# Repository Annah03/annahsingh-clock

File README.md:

# annahsingh-clock
 My first HPS clock.

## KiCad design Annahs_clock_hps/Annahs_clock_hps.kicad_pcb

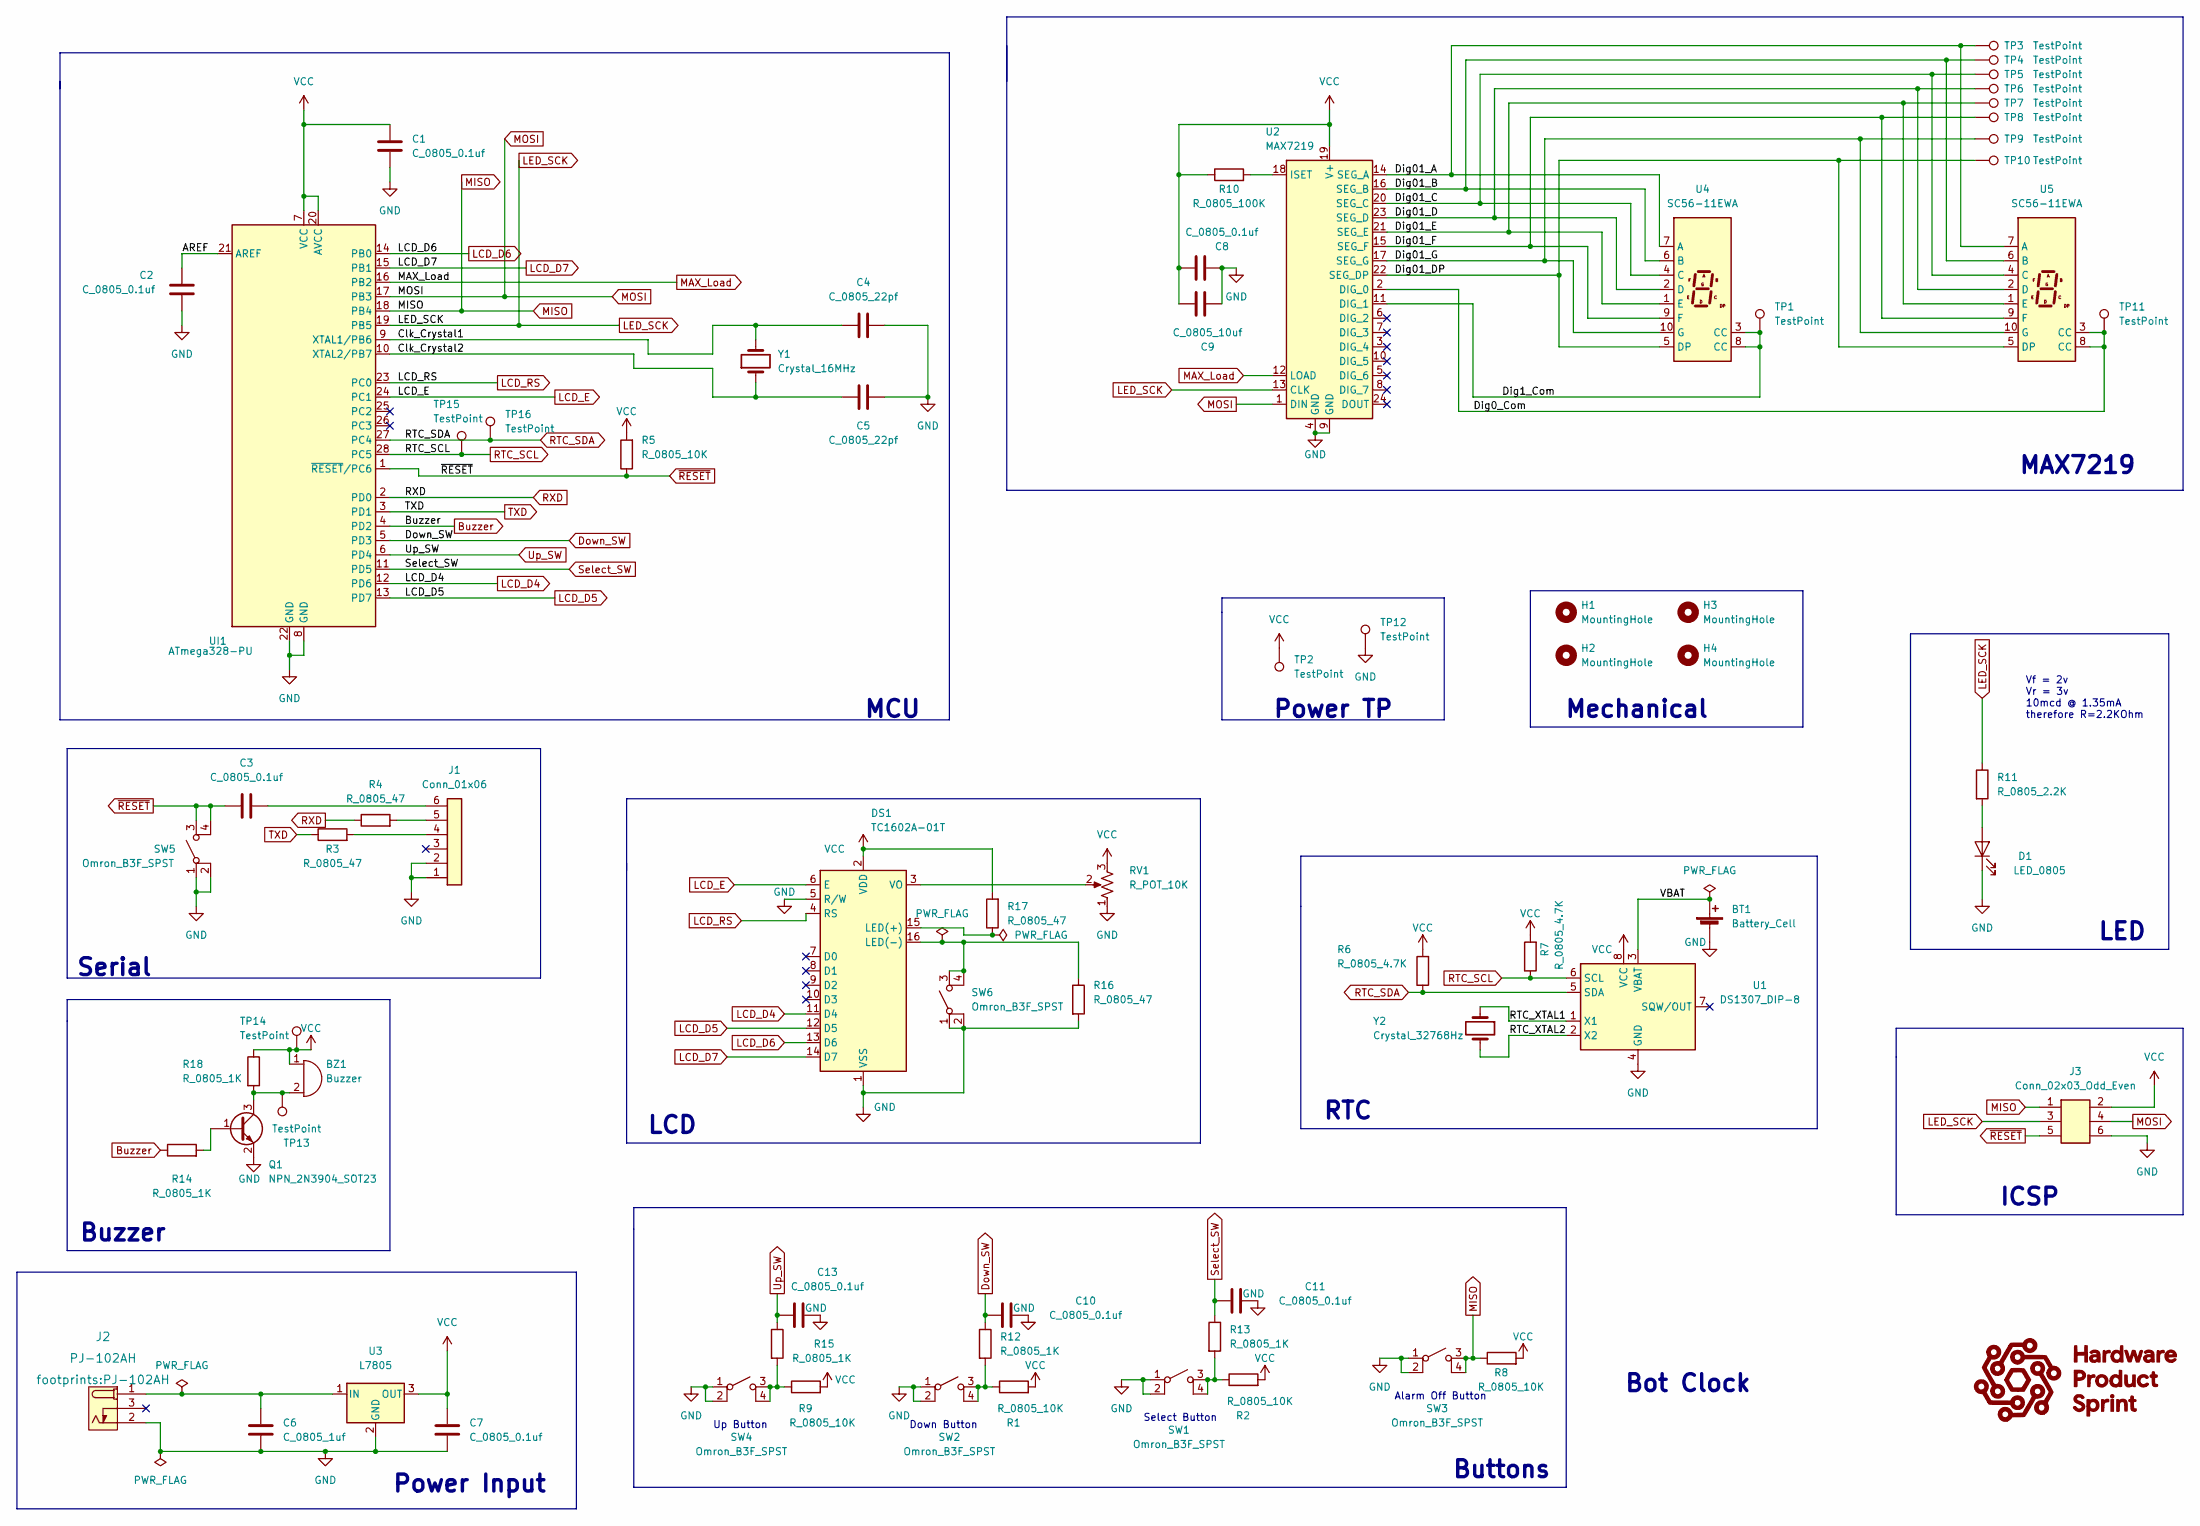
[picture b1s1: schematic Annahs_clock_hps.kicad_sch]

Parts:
BT1: Battery_Cell; BatteryHolder_Keystone_106_1x20mm; MPN BS-7; Digikey PN BS-7-ND
BZ1: Buzzer; Buzzer_TDK_PS1240P02BT_D12.2mm_H6.5mm; MPN PS1420P02CT; Digikey PN 445-2526-1-ND
C1, C2, C3, C7, C8, C10, C11, C13: C_0805_0.1uf; C_0805_2012Metric; Voltage N/A; Tolerance N/A; MPN 08055C104KAT2A; Digikey PN 478-1395-1-ND
C4, C5: C_0805_22pf; C_0805_2012Metric; Voltage N/A; Tolerance N/A; MPN CC0805JRNPO9BN220; Digikey PN 311-1103-1-ND
C6: C_0805_1uf; C_0805_2012Metric; Voltage N/A; Tolerance N/A; MPN CC0805KKX7R8BB105; Digikey PN 311-1456-1-ND
C9: C_0805_10uf; C_0805_2012Metric; Voltage N/A; Tolerance N/A; MPN GRM21BR61E106KA73L; Digikey PN 490-5523-1-ND
D1: LED_0805; LED_0805_2012Metric; MPN 150080RS75000; Digikey PN 732-4984-1-ND
DS1: TC1602A-01T; MPN 1447; Digikey PN 1528-2212-ND
H1, H2, H3, H4: MountingHole; MountingHole_3.2mm_M3
J1: Conn_01x06; PinHeader_1x06_P2.54mm_Vertical; MPN 61300611121; Digikey PN 732-5319-ND
J2: PJ-102AH; MPN PJ-102AH; Digikey PN CP-102AH-ND
J3: Conn_02x03_Odd_Even; PinHeader_2x03_P2.54mm_Vertical; MPN PRPC003DAAN-RC; Digikey PN S2011EC-03-ND
Q1: NPN_2N3904_SOT23; SOT-23; MPN CMPT3904E TR PBFREE; Digikey PN 1514-CMPT3904ETRPBFREECT-ND
R1, R2, R5, R8, R9: R_0805_10K; R_0805_2012Metric; Tolerance N/A; MPN RC0805FR-0710KL; Digikey PN 311-10.0KCRCT-ND
R3, R4, R16, R17: R_0805_47; R_0805_2012Metric; Tolerance N/A; Mouser PN N/A; Digikey PN RC0805FR-0747RL
R6, R7: R_0805_4.7K; R_0805_2012Metric; Tolerance N/A; MPN RC0805FR-074K7L; Digikey PN 311-4.70KCRCT-ND
R10: R_0805_100K; R_0805_2012Metric; Tolerance N/A; MPN RC0805FR-07100KL; Digikey PN 311-100KCRCT-ND
R11: R_0805_2.2K; R_0805_2012Metric; Tolerance N/A; MPN N/A; Digikey PN 311-2.20KCRCT-ND
R12, R13, R14, R15, R18: R_0805_1K; R_0805_2012Metric; Tolerance N/A; Mouser PN N/A; Digikey PN RC0805FR-0710KL
RV1: R_POT_10K; Potentiometer_Bourns_3386P_Vertical; MPN 3386P-1-103TLF; Digikey PN 3386P-103TLF-ND
SW1, SW2, SW3, SW4, SW5, SW6: Omron_B3F_SPST; SW_SPST_Omron_B3FS-100xP; MPN B3FS-1000P; Digikey PN SW423CT-ND
TP1, TP2, TP3, TP4, TP5, TP6, TP7, TP8, TP9, TP10, TP11, TP12, TP13, TP14, TP15, TP16: TestPoint; TestPoint_THTPad_D2.0mm_Drill1.0mm
U1: DS1307_DIP-8; DIP-8_W7.62mm; MPN A 08-LC-TT; Digikey PN AE9986-ND
U2: MAX7219; DIP-24_W7.62mm; MPN ED241DT; Digikey PN ED3049-5-ND
U3: L7805; TO-252-2; MPN L7805CDT-TR; Digikey PN 497-7255-1-ND
U4, U5: SC56-11EWA; Sx56-1xxxxx; Digikey PN 754-1465-5-ND
UI1: ATmega328-PU; DIP-28_W7.62mm; MPN ED281DT; Digikey PN ED3050-5-ND
Y1: Crystal_16MHz; Crystal_SMD_HC49-SD; MPN ECS-160-20-5PXDN-TR; Digikey PN XC1299CT-ND
Y2: Crystal_32768Hz; Crystal_SMD_2Pin_3.2x1.5mm; MPN Q 0,032768-JTX310-12,5-20-T1-HMR-50K-LF; Digikey PN 1908-1314-1-ND

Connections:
/AREF: C2.1, UI1.21 (AREF)
/Clk_Crystal1: C4.2, UI1.9 (XTAL1/PB6), Y1.2
/Clk_Crystal2: C5.1, UI1.10 (XTAL2/PB7), Y1.1
/Dig0_Com: TP11.1, U2.2 (DIG_0), U5.3 (CC), U5.8 (CC)
/Dig01_A: TP3.1, U2.14 (SEG_A), U4.7 (A), U5.7 (A)
/Dig01_B: TP4.1, U2.16 (SEG_B), U4.6 (B), U5.6 (B)
/Dig01_C: TP5.1, U2.20 (SEG_C), U4.4 (C), U5.4 (C)
/Dig1_Com: TP1.1, U2.11 (DIG_1), U4.3 (CC), U4.8 (CC)
/Dig01_D: TP6.1, U2.23 (SEG_D), U4.2 (D), U5.2 (D)
/Dig01_DP: TP10.1, U2.22 (SEG_DP), U4.5 (DP), U5.5 (DP)
/Dig01_E: TP7.1, U2.21 (SEG_E), U4.1 (E), U5.1 (E)
/Dig01_F: TP8.1, U2.15 (SEG_F), U4.9 (F), U5.9 (F)
/Dig01_G: TP9.1, U2.17 (SEG_G), U4.10 (G), U5.10 (G)
/RTC_XTAL1: U1.1 (X1), Y2.1
/RTC_XTAL2: U1.2 (X2), Y2.2
/VBAT: BT1.1 (+), U1.3 (VBAT)
Buzzer: R14.1, UI1.4 (PD2)
Down_SW: C10.2, R12.1, UI1.5 (PD3)
GND: BT1.2 (-), C1.2, C2.2, C4.1, C5.2, C6.2, C7.2, C8.2, C9.2, C10.1, C11.1, C13.1, D1.1 (K), DS1.1 (VSS), DS1.5 (R/W), J1.1, J1.2, J2.2 (OUT), J3.6, Q1.2 (E), R16.2, RV1.1, SW1.1 (A), SW1.2 (A), SW2.1 (A), SW2.2 (A), SW3.1 (A), SW3.2 (A), SW4.1 (A), SW4.2 (A), SW5.1 (A), SW5.2 (A), SW6.1 (A), SW6.2 (A), TP12.1, U1.4 (GND), U2.4 (GND), U2.9 (GND), U3.2 (GND), UI1.8 (GND), UI1.22 (GND)
LCD_D4: DS1.11 (D4), UI1.12 (PD6)
LCD_D5: DS1.12 (D5), UI1.13 (PD7)
LCD_D6: DS1.13 (D6), UI1.14 (PB0)
LCD_D7: DS1.14 (D7), UI1.15 (PB1)
LCD_E: DS1.6 (E), UI1.24 (PC1)
LCD_RS: DS1.4 (RS), UI1.23 (PC0)
LED_SCK: J3.3, R11.1, U2.13 (CLK), UI1.19 (PB5)
MAX_Load: U2.12 (LOAD), UI1.16 (PB2)
MISO: J3.1, R8.1, SW3.3 (B), SW3.4 (B), UI1.18 (PB4)
MOSI: J3.4, U2.1 (DIN), UI1.17 (PB3)
unnamed: BZ1.2 (+), Q1.3 (C), R18.2, TP13.1
unnamed: C3.2, J1.6
unnamed: C6.1, J2.1 (POLE), U3.1 (IN)
unnamed: D1.2 (A), R11.2
unnamed: DS1.3 (VO), RV1.2
unnamed: DS1.15 (LED(+)), R17.1
unnamed: DS1.16 (LED(-)), R16.1, SW6.3 (B), SW6.4 (B)
unnamed: J1.4, R3.2
unnamed: J1.5, R4.2
unnamed: Q1.1 (B), R14.2
unnamed: R1.1, R12.2, SW2.3 (B), SW2.4 (B)
unnamed: R10.2, U2.18 (ISET)
unnamed: R2.1, R13.2, SW1.3 (B), SW1.4 (B)
unnamed: R9.1, R15.2, SW4.3 (B), SW4.4 (B)
RTC_SCL: R7.1, TP15.1, U1.6 (SCL), UI1.28 (PC5)
RTC_SDA: R6.1, TP16.1, U1.5 (SDA), UI1.27 (PC4)
RXD: R4.1, UI1.2 (PD0)
Select_SW: C11.2, R13.1, UI1.11 (PD5)
TXD: R3.1, UI1.3 (PD1)
Up_SW: C13.2, R15.1, UI1.6 (PD4)
VCC: BZ1.1 (-), C1.1, C7.1, C8.1, C9.1, DS1.2 (VDD), J3.2, R1.2, R2.2, R5.2, R6.2, R7.2, R8.2, R9.2, R10.1, R17.2, R18.1, RV1.3, TP2.1, TP14.1, U1.8 (VCC), U2.19 (V+), U3.3 (OUT), UI1.7 (VCC), UI1.20 (AVCC)
~RESET: C3.1, J3.5, R5.1, SW5.3 (B), SW5.4 (B), UI1.1 (~RESET/PC6)

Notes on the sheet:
MCU
Down Button
Select Button
Mechanical
MAX7219
Power TP
LCD
Power Input
Buttons
Serial
Alarm Off Button
LED
RTC
Up Button
Vf = 2v Vr = 3v 10mcd @ 1.35mA therefore R=2.2KOhm
Bot Clock
ICSP
Buzzer

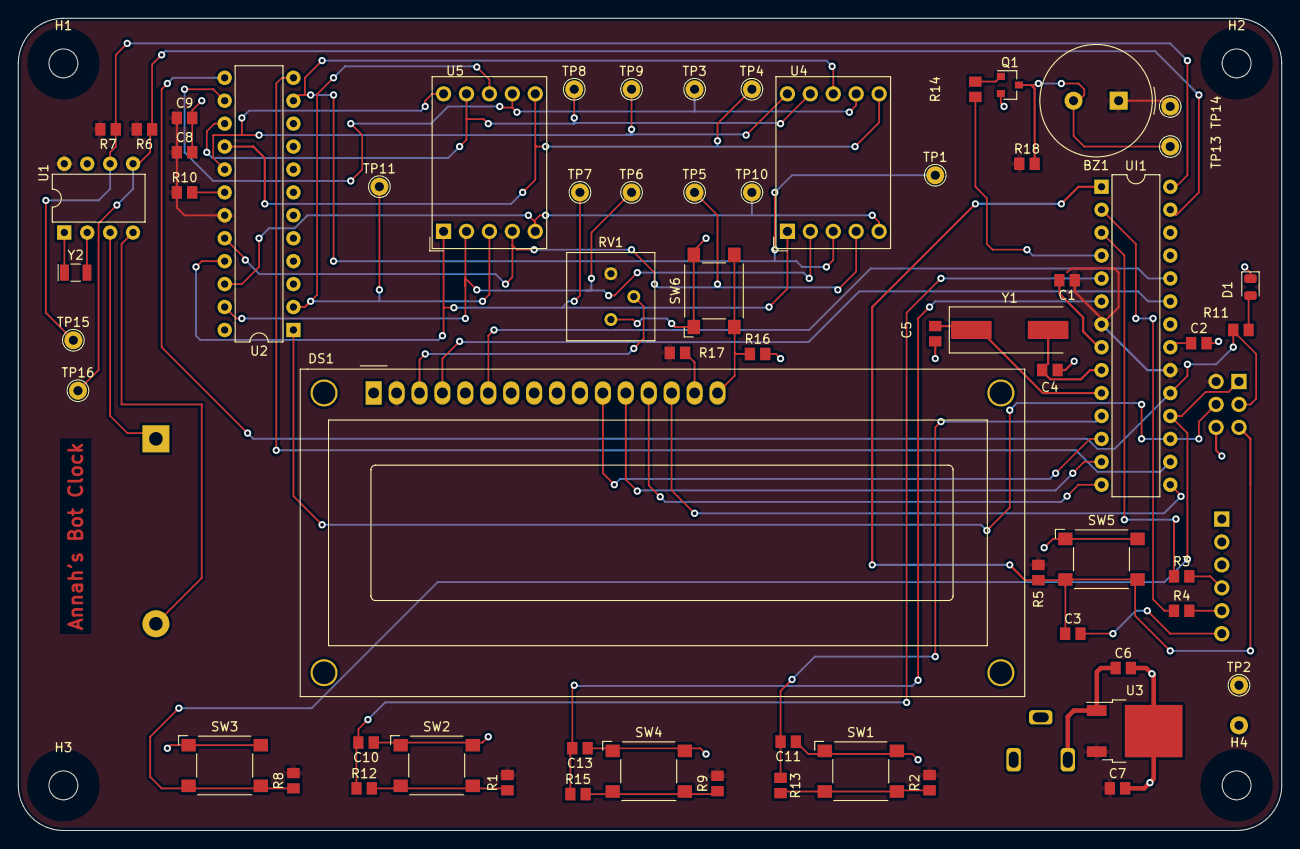
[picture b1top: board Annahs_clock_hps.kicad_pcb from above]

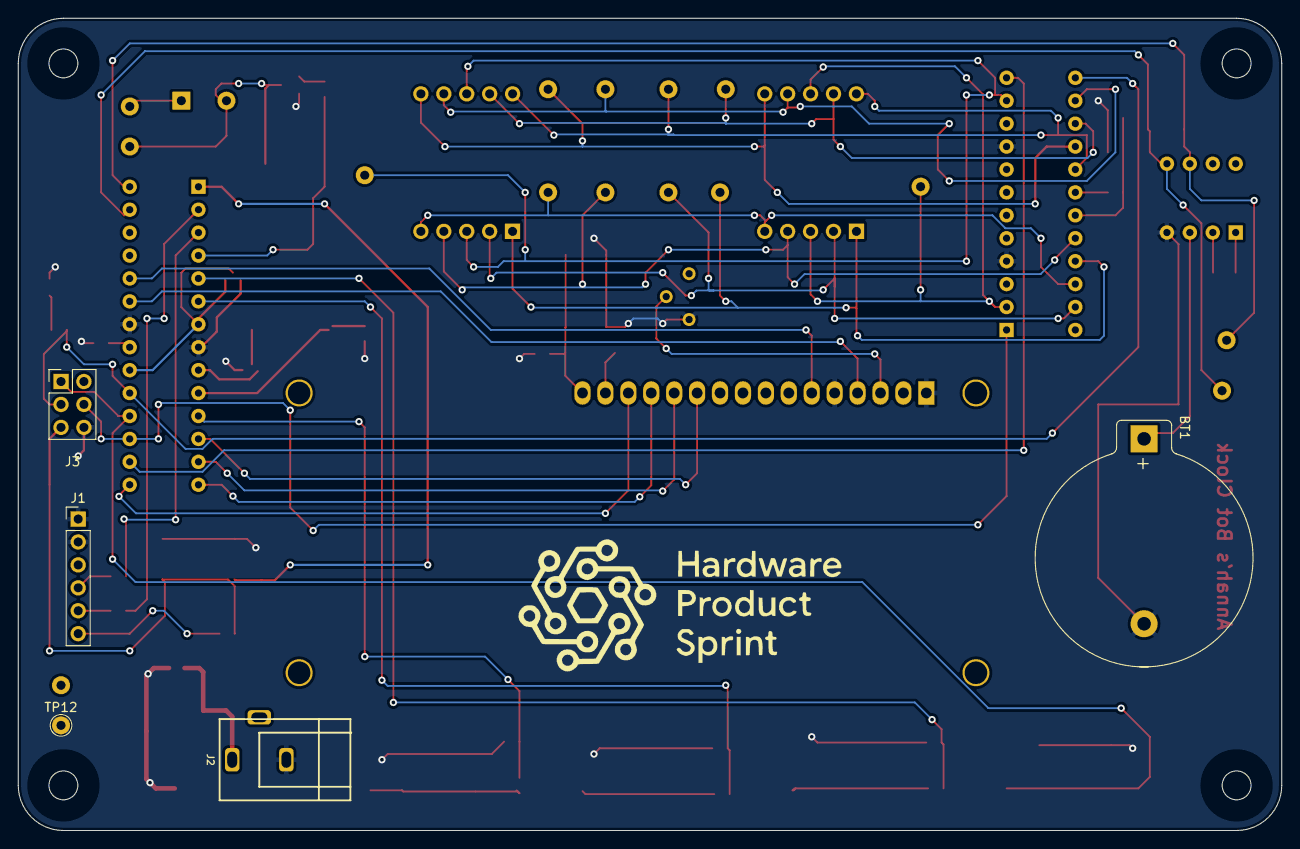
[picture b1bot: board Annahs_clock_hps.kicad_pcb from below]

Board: 2 copper layers, 140.0 x 90.0 mm, 73 parts (5 on the bottom side), 51 nets.

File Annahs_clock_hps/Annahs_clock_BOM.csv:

"Id";"Designator";"Package";"Quantity";"Designation";"Supplier and ref";
1;"C6";"C_0805_2012Metric";1;"C_0805_1uf";;;
2;"H4,H2,H3,H1";"MountingHole_3.2mm_M3";4;"MountingHole";;;
3;"R6,R7";"R_0805_2012Metric";2;"R_0805_4.7K";;;
4;"RV1";"Potentiometer_Bourns_3386P_Vertical";1;"R_POT_10K";;;
5;"Y2";"Crystal_SMD_2Pin_3.2x1.5mm";1;"Crystal_32768Hz";;;
6;"TP9,TP7,TP5,TP14,TP10,TP4,TP1,TP6,TP2,TP3,TP13,TP11,TP8,TP12";"TestPoint_THTPad_D2.0mm_Drill1.0mm";14;"TestPoint";;;
7;"R17,R16,R4,R3";"R_0805_2012Metric";4;"R_0805_47";;;
8;"U3";"TO-252-2";1;"L7805";;;
9;"R14,R11";"R_0805_2012Metric";2;"R_0805_2.2K";;;
10;"U5,U4";"Sx56-1xxxxx";2;"SC56-11EWA";;;
11;"R5,R1,R8,R9,R2";"R_0805_2012Metric";5;"R_0805_10K";;;
12;"C2,C10,C8,C7,C11,C13,C3,C1";"C_0805_2012Metric";8;"C_0805_0.1uf";;;
13;"R10";"R_0805_2012Metric";1;"R_0805_100K";;;
14;"U2";"DIP-24_W7.62mm";1;"MAX7219";;;
15;"Q1";"SOT-23";1;"NPN_2N3904_SOT23";;;
16;"D1";"LED_0805_2012Metric";1;"LED_0805";;;
17;"R13,R15,R12";"R_0805_2012Metric";3;"R_0805_1K";;;
18;"SW6,SW2,SW1,SW3,SW4,SW5";"SW_SPST_Omron_B3FS-100xP";6;"Omron_B3F_SPST";;;
19;"U1";"DIP-8_W7.62mm";1;"DS1307_DIP-8";;;
20;"Y1";"Crystal_SMD_HC49-SD";1;"Crystal_16MHz";;;
21;"BZ1";"Buzzer_TDK_PS1240P02BT_D12.2mm_H6.5mm";1;"Buzzer";;;
22;"J1";"PinHeader_1x06_P2.54mm_Vertical";1;"Conn_01x06";;;
23;"J3";"PinHeader_2x03_P2.54mm_Vertical";1;"Conn_02x03_Odd_Even";;;
24;"C4,C5";"C_0805_2012Metric";2;"C_0805_22pf";;;
25;"UI1";"DIP-28_W7.62mm";1;"ATmega328-PU";;;
26;"C9";"C_0805_2012Metric";1;"C_0805_10uf";;;
27;"BT1";"BatteryHolder_Keystone_106_1x20mm";1;"Battery_Cell";;;
28;"DS1";"TC1602A-01T";1;"TC1602A-01T";;;
29;"J2";"Wurth-694106402002";1;"Power_inlet_vertical";;;

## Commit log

2022-05-30 My First Design Commit
2022-06-09 Slide 39
2022-06-10 Schematic Phase I
2022-06-16 Schematic Week 1/2 Update
2022-06-16 Week 1/2 Schematic Update
2022-06-18 Updated Schematic Week1/2
2022-06-19 Changing Serial Output
2022-06-23 Clock Schematic
2022-06-25 Real Time Clock
2022-07-03 Update_Schematic
2022-07-03 Updated_Schematic
2022-07-03 Schematic Update
2022-07-03 LCD_Teeth_Code
2022-07-03 Displays_firmware
2022-07-03 Clock Schematic and PCB
2022-07-04 Updated Schematic and PCB
2022-07-04 Update_PCB
2022-07-05 Backup Folder Removed
2022-07-05 Updated Footprint Schematic and PCB
2022-07-06 Updated Schematic
2022-07-06 Backup Removal
2022-07-06 Removal Of Backups
2022-07-09 PCB and Schematic Updated
2022-07-09 Firmware
2022-07-12 PCB Routing
2022-07-17 Rendering Screenshot
2022-07-17 Gerber, BOM, Drill, and Component Files
2022-07-17 STEP File
2022-07-17 Schematic and PCB Updates
2022-07-17 Reorganization of Files
2022-07-17 PCB Updates
2022-07-18 Updated PCB and Schematic
2022-07-18 Updated Gerber, STEP, BOM
2022-07-19 Undo Re-Organization
2022-07-19 Undo Reorganization
2022-07-19 Schematic and PCB Update
2022-07-21 Updated STEP
2022-07-21 Updated PCB/Schematic/Gerber
2022-07-21 PCB and Schematic Fixes
2022-07-21 Gerber Files
2022-07-21 PCB and Schematic Updates
2022-07-21 Backups
2022-07-21 Clock BOM
2022-07-21 3D View of Clock
2022-07-21 Miscellaneous Updates
2022-07-25 Start of Complete Firmware
2022-07-25 void setTime() addition to firmware
2022-07-27 Firmware for MTP
2022-07-31 MTP Firmware
2022-07-31 MTP FIrmware Alarm
2022-08-09 Firmware Updates
2022-09-28 Complete Firmware Update
